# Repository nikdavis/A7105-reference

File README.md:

This is the board design for a micro FlySky radio based on the A7105. See sibling project for software.

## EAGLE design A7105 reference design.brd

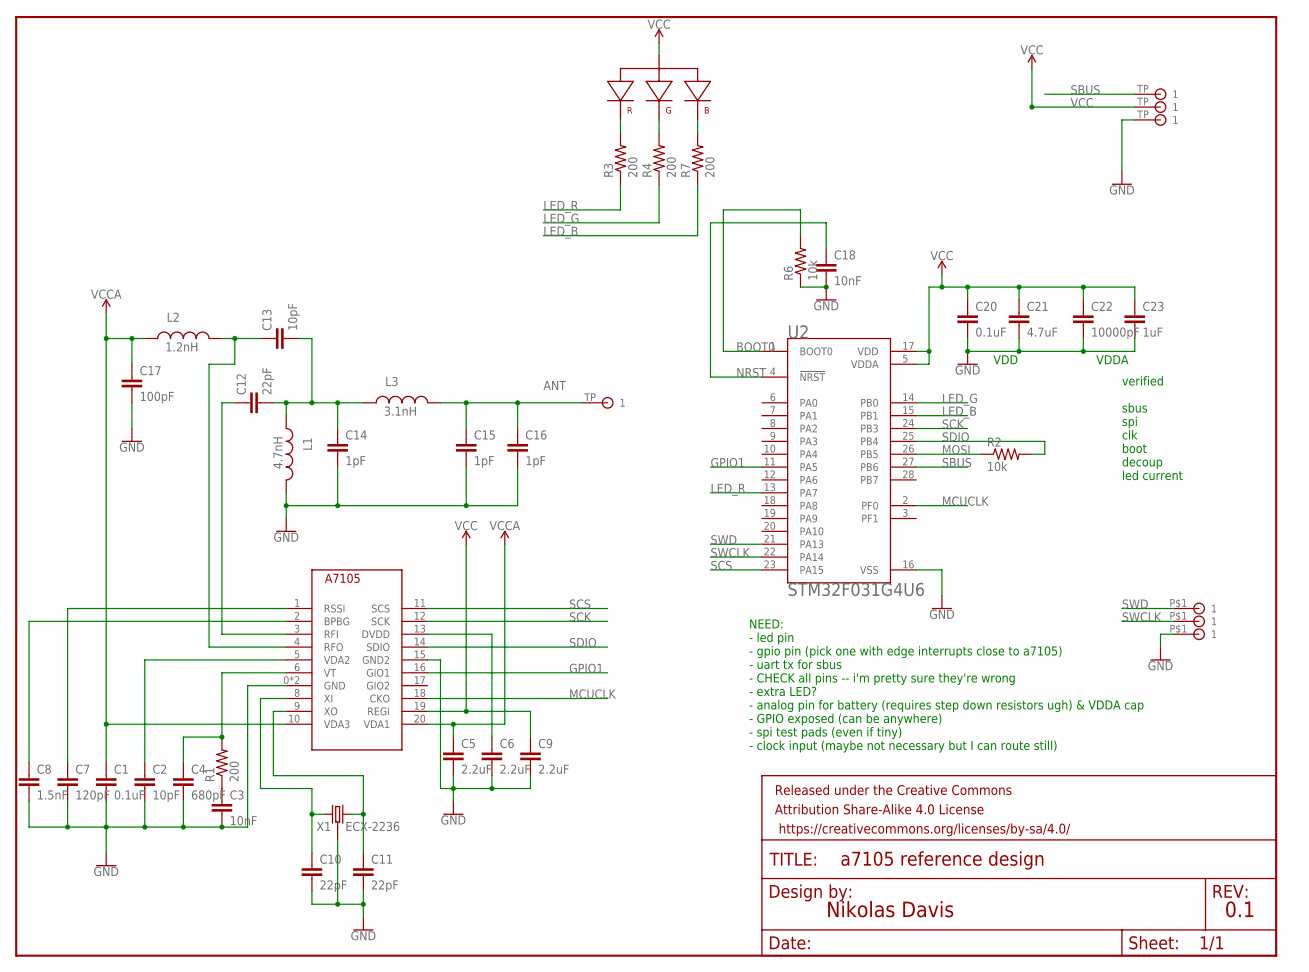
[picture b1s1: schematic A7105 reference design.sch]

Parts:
ANT: TESTPAD
C1, C20: 0.1uF; 0402
C2, C13: 10pF; 0402
C3, C18: 10nF; 0402
C4: 680pF; 0402
C5, C6, C9: 2.2uF; 0402
C7: 120pF; 0402
C8: 1.5nF; 0402
C10, C11, C12: 22pF; 0402
C14, C15, C16: 1pF; 0402
C17: 100pF; 0402
C21: 4.7uF; 0402
C22: 10000pF; 0402
C23: 1uF; 0402
FRAME1: FRAME-LETTER; CREATIVE_COMMONS
L1: 4.7nH; 0402
L2: 1.2nH; 0402
L3: 3.1nH; 0402
LED1: RGBLED_CANODE; SML-LX0404SIUPGUSB
R1, R3, R4, R7: 200; 0402
R2, R6: 10k; 0402
TP1, TP2, TP3: TESTPAD; SMTPAD-RECT
U1: A7105; QFN20-4X4MM
U2: STM32F031G4U6; QFN50P400X400X60-28N
U$6, U$8, U$9: TESTPAD
X1: ECX-2236; 2.5X2.0MM_CRYSTAL

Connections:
ANT: ANT.TP, C15.1, C16.1, L3.2
BOOT0: R6.2, U2.1 (BOOT0)
GND: C1.2, C2.2, C3.2, C4.2, C5.2, C6.2, C7.2, C8.2, C9.2, C10.2, C11.2, C14.2, C15.2, C16.2, C17.2, C18.2, C20.2, C21.2, C22.2, C23.2, L1.2, R6.1, TP3.P$1, U1.0 (GND), U1.7 (GND), U1.15 (GND2), U2.16 (VSS), U$9.TP, X1.P$2 (3), X1.P$4 (3)
GPIO1: U1.16 (GIO1), U2.11 (PA5)
LED_B: R7.1, U2.15 (PB1)
LED_G: R4.1, U2.14 (PB0)
LED_R: R3.1, U2.13 (PA7)
MCUCLK: U1.18 (CKO), U2.2 (PF0)
MOSI: R2.1, U2.26 (PB5)
unnamed: C2.1, U1.5 (VDA2)
unnamed: C3.1, R1.1
unnamed: C4.1, R1.2, U1.6 (VT)
unnamed: C6.1, U1.13 (DVDD)
unnamed: C7.1, U1.1 (RSSI)
unnamed: C8.1, U1.2 (BPBG)
unnamed: C11.1, U1.9 (XO), X1.P$3 (2)
unnamed: C12.2, C13.2, C14.1, L1.1, L3.1
unnamed: C10.1, U1.8 (XI), X1.P$1 (1)
unnamed: LED1.P$2 (R_P2), R3.2
unnamed: LED1.P$4 (G_P4), R4.2
unnamed: LED1.P$3 (B_P3), R7.2
NRST: C18.1, U2.4 (!NRST)
RFI: C12.1, U1.3 (RFI)
RFO: C13.1, L2.2, U1.4 (RFO)
SBUS: U2.27 (PB6), U$6.TP
SCK: U1.12 (SCK), U2.24 (PB3)
SCS: U1.11 (SCS), U2.23 (PA15)
SDIO: R2.2, U1.14 (SDIO), U2.25 (PB4)
SWCLK: TP2.P$1, U2.22 (PA14)
SWD: TP1.P$1, U2.21 (PA13)
VCC: C9.1, C20.1, C21.1, C22.1, C23.1, LED1.P$1 (AN_P1), U1.19 (REGI), U2.5 (VDDA), U2.17 (VDD), U$8.TP
VCCA: C1.1, C5.1, C17.1, L2.1, U1.10 (VDA3), U1.20 (VDA1)

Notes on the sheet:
Nikolas Davis
0.1
NEED: - led pin - gpio pin (pick one with edge interrupts close to a7105) - uart tx for sbus - CHECK all pins -- i'm pretty sure they're wrong - extra LED? - analog pin for battery (requires step down resistors ugh) & VDDA cap - GPIO exposed (can be anywhere) - spi test pads (even if tiny) - clock 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
VDDA
VDD
verified sbus spi clk boot decoup led current

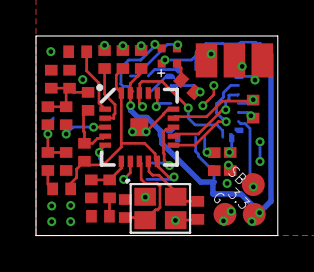
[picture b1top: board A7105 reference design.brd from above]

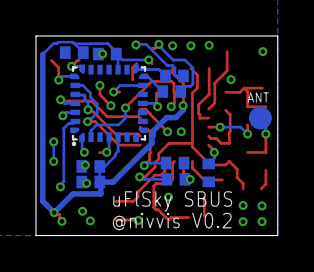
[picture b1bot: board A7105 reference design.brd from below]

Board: 2 copper layers, 13.4 x 11.1 mm, 43 parts (11 on the bottom side), 32 nets.

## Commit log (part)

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2019-02-23 Finished integrated rev 0.2
2019-02-23 Cleanup before order
2019-02-23 Add bind pull up
2019-02-24 Start STM rehaul -- stuck on EEPROM decision
2019-03-01 Fix pads and more, rev 0.3
2019-03-03 Small edits
    Bit of board prep organization. Small schematic clean up and notes.
2019-03-03 Moving stuff around?
2019-03-07 First steps
    Remove inverter
    Make todo list
2019-03-07 Blank readme
2019-03-08 STM work
2019-03-08 STM "ready"

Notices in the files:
parts and their libraries:
SparkFun-Aesthetics: Licensing: Creative Commons ShareAlike 4.0 International - https://creativecommons.org/licenses/by-sa/4.0
SparkFun-Aesthetics: Released under the Creative Commons Attribution Share-Alike 4.0 License
SparkFun-Aesthetics: https://creativecommons.org/licenses/by-sa/4.0
